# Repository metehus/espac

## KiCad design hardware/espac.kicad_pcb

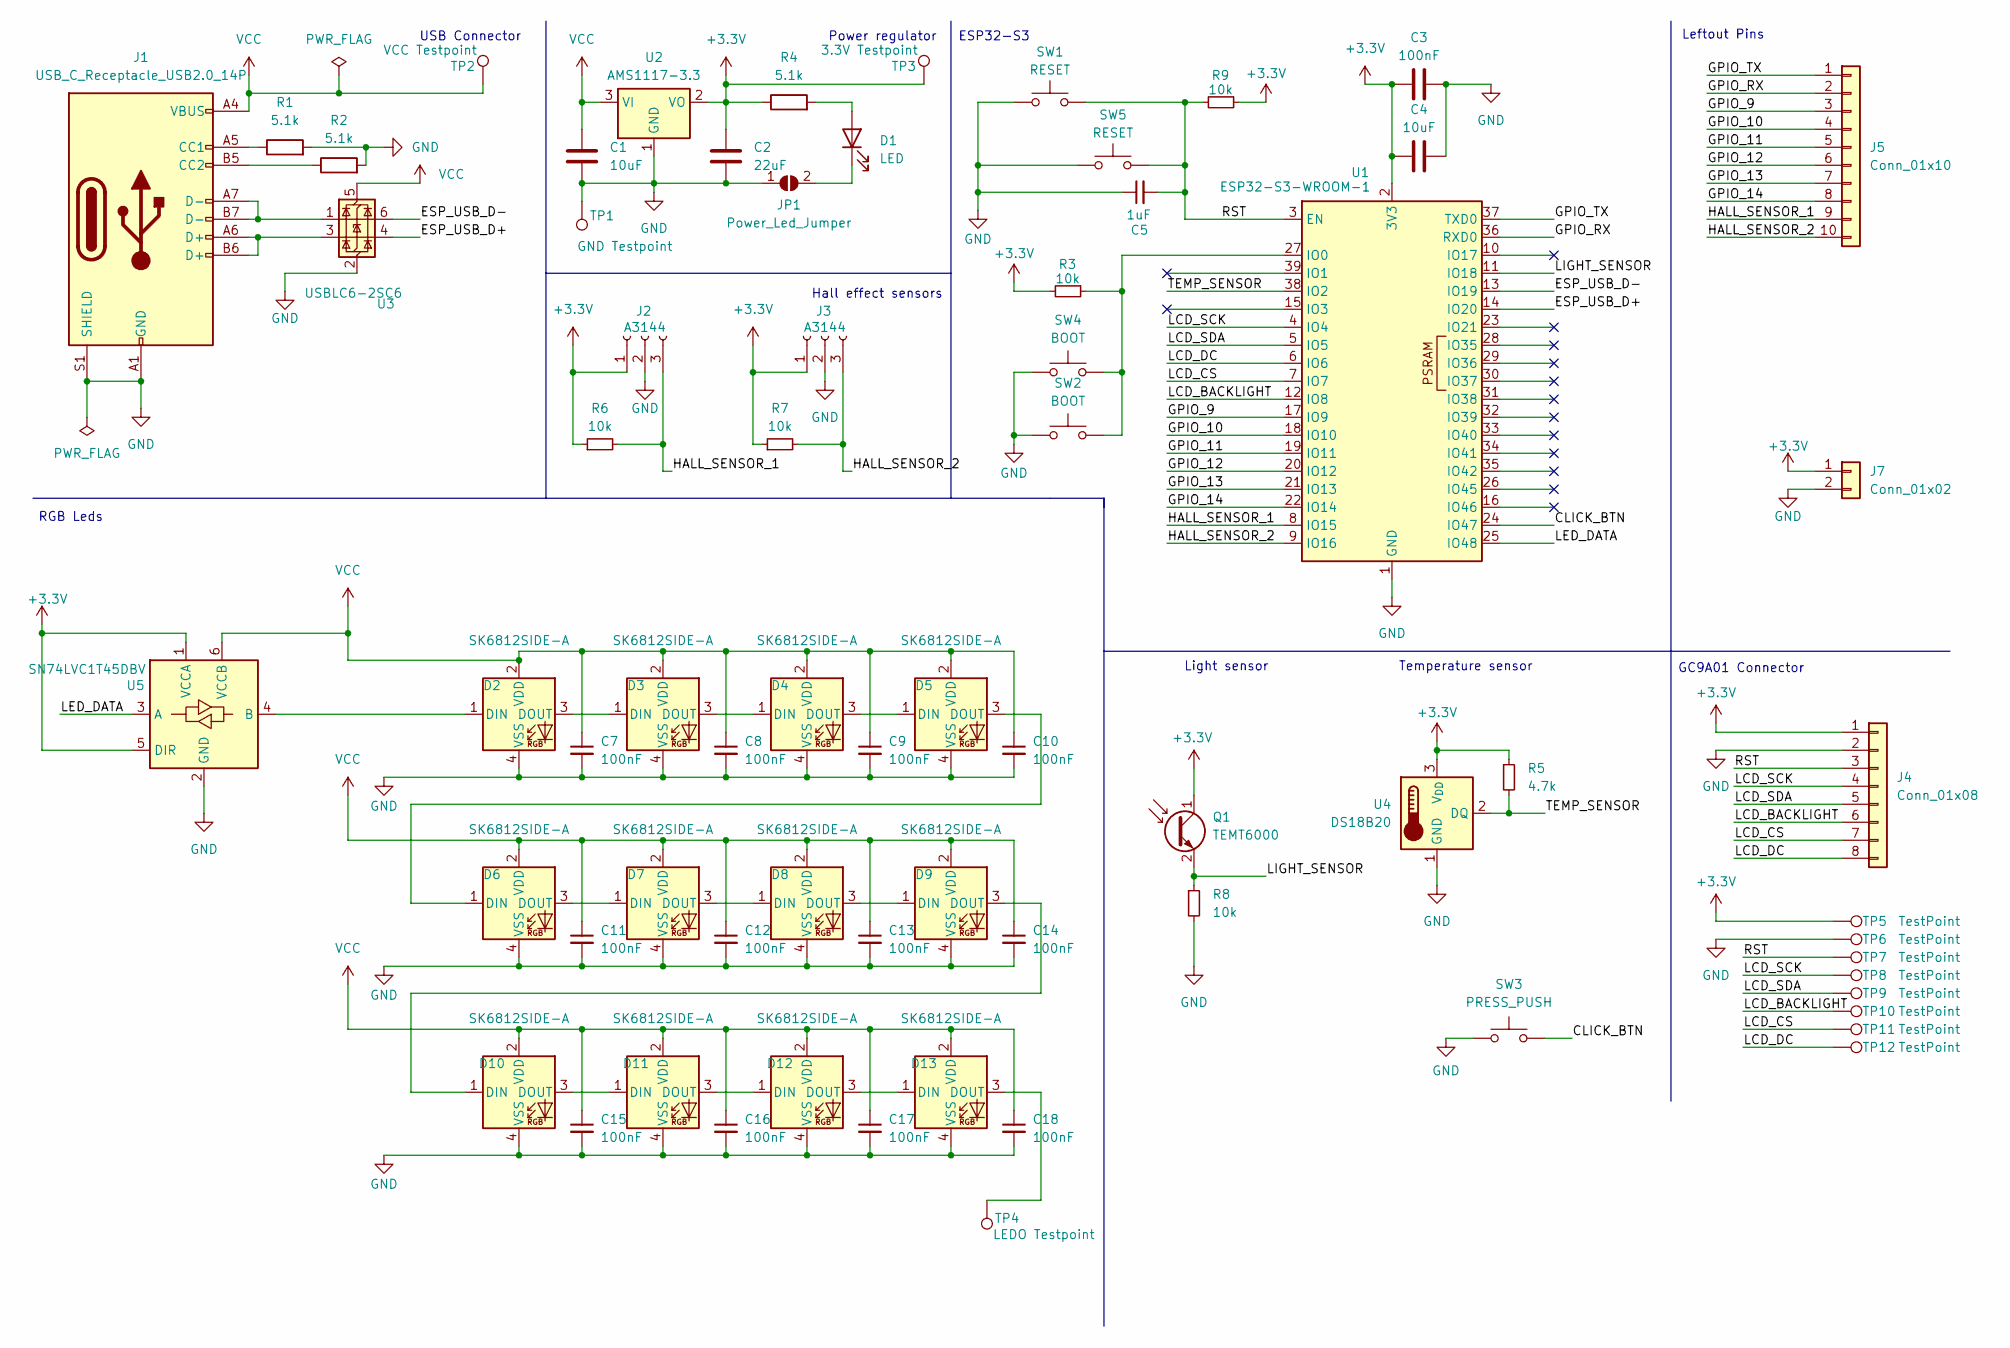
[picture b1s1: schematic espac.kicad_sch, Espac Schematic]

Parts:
C1, C4: 10uF; C_0805_2012Metric_Pad1.18x1.45mm_HandSolder
C2: 22uF; C_0805_2012Metric_Pad1.18x1.45mm_HandSolder
C3, C7, C8, C9, C10, C11, C12, C13, C14, C15, C16, C17, C18: 100nF; C_0805_2012Metric_Pad1.18x1.45mm_HandSolder
C5: 1uF; C_0805_2012Metric_Pad1.18x1.45mm_HandSolder
D1: LED; LED_0603_1608Metric_Pad1.05x0.95mm_HandSolder
D2, D3, D4, D5, D6, D7, D8, D9, D10, D11, D12, D13: SK6812SIDE-A; SK6812-SIDE-A
J1: USB_C_Receptacle_USB2.0_14P; USB_C_Receptacle_G-Switch_GT-USB-7010ASV
J2, J3: A3144; JST_GH_SM03B-GHS-TB_1x03-1MP_P1.25mm_Horizontal
J4: Conn_01x08; TE_0-1734839-8_1x08-1MP_P0.5mm_Horizontal
J5: Conn_01x10; PinSocket_1x10_P2.54mm_Vertical
J7: Conn_01x02; PinHeader_1x02_P2.54mm_Vertical
JP1: Power_Led_Jumper; SolderJumper-2_P1.3mm_Open_RoundedPad1.0x1.5mm
Q1: TEMT6000
R1, R2, R4: 5.1k; R_0603_1608Metric
R3, R6, R7, R8, R9: 10k; R_0603_1608Metric
R5: 4.7k; R_0603_1608Metric
SW1: RESET; SMD_SIDED_TACT_SWITCH
SW2: BOOT; SMD_SIDED_TACT_SWITCH
SW3: PRESS_PUSH; SW_PUSH_6mm_H4.3mm
SW4: BOOT; SMD_TACT_SWITCH
SW5: RESET; SMD_TACT_SWITCH
TP1: GND Testpoint; TestPoint_Pad_D1.5mm
TP2: VCC Testpoint; TestPoint_Pad_D1.5mm
TP3: 3.3V Testpoint; TestPoint_Pad_D1.5mm
TP4: LEDO Testpoint; TestPoint_Pad_D1.5mm
TP5, TP6, TP7, TP8, TP9, TP10, TP11, TP12: TestPoint; TestPoint_Pad_D1.5mm
U1: ESP32-S3-WROOM-1
U2: AMS1117-3.3; SOT-223-3_TabPin2
U3: USBLC6-2SC6; SOT-23-6
U4: DS18B20; TO-92_Inline
U5: SN74LVC1T45DBV; SOT-23-6_Handsoldering

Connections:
+3.3V: C2.1, C3.1, C4.1, J2.1, J3.1, J4.1, J7.1, Q1.1 (C), R3.2, R4.1, R5.1, R6.1, R7.1, R9.1, TP3.1, TP5.1, U1.2 (3V3), U2.2 (VO), U4.3 (V_{DD}), U5.1 (VCCA), U5.5 (DIR)
/CLICK_BTN: SW3.2, U1.24 (IO47)
/ESP_USB_D+: U1.14 (IO20), U3.4 (I/O2)
/ESP_USB_D-: U1.13 (IO19), U3.6 (I/O1)
/GPIO_9: J5.3, U1.17 (IO9)
/GPIO_10: J5.4, U1.18 (IO10)
/GPIO_11: J5.5, U1.19 (IO11)
/GPIO_12: J5.6, U1.20 (IO12)
/GPIO_13: J5.7, U1.21 (IO13)
/GPIO_14: J5.8, U1.22 (IO14)
/GPIO_RX: J5.2, U1.36 (RXD0)
/GPIO_TX: J5.1, U1.37 (TXD0)
/HALL_SENSOR_1: J2.3, J5.9, R6.2, U1.8 (IO15)
/HALL_SENSOR_2: J3.3, J5.10, R7.2, U1.9 (IO16)
/LCD_BACKLIGHT: J4.6, TP10.1, U1.12 (IO8)
/LCD_CS: J4.7, TP11.1, U1.7 (IO7)
/LCD_DC: J4.8, TP12.1, U1.6 (IO6)
/LCD_SCK: J4.4, TP8.1, U1.4 (IO4)
/LCD_SDA: J4.5, TP9.1, U1.5 (IO5)
/LED_DATA: U1.25 (IO48), U5.3 (A)
/LIGHT_SENSOR: Q1.2 (E), R8.1, U1.11 (IO18)
/RST: C5.2, J4.3, R9.2, SW1.2, SW5.1, TP7.1, U1.3 (EN)
/TEMP_SENSOR: R5.2, U1.38 (IO2), U4.2 (DQ)
GND: C1.2, C2.2, C3.2, C4.2, C5.1, C7.2, C8.2, C9.2, C10.2, C11.2, C12.2, C13.2, C14.2, C15.2, C16.2, C17.2, C18.2, D2.4 (VSS), D3.4 (VSS), D4.4 (VSS), D5.4 (VSS), D6.4 (VSS), D7.4 (VSS), D8.4 (VSS), D9.4 (VSS), D10.4 (VSS), D11.4 (VSS), D12.4 (VSS), D13.4 (VSS), J1.A1 (GND), J1.A12 (GND), J1.B1 (GND), J1.B12 (GND), J1.S1 (SHIELD), J2.2, J3.2, J4.2, J7.2, JP1.1 (A), R1.2, R2.2, R8.2, SW1.1, SW2.1, SW3.1, SW4.2, SW5.2, TP1.1, TP6.1, U1.1 (GND), U1.40 (GND), U1.41 (GND), U2.1 (GND), U3.2 (GND), U4.1 (GND), U5.2 (GND)
unnamed: D1.2 (A), R4.2
unnamed: D1.1 (K), JP1.2 (B)
unnamed: D2.1 (DIN), U5.4 (B)
unnamed: D2.3 (DOUT), D3.1 (DIN)
unnamed: D3.3 (DOUT), D4.1 (DIN)
unnamed: D4.3 (DOUT), D5.1 (DIN)
unnamed: D5.3 (DOUT), D6.1 (DIN)
unnamed: D6.3 (DOUT), D7.1 (DIN)
unnamed: D7.3 (DOUT), D8.1 (DIN)
unnamed: D8.3 (DOUT), D9.1 (DIN)
unnamed: D9.3 (DOUT), D10.1 (DIN)
unnamed: D10.3 (DOUT), D11.1 (DIN)
unnamed: D11.3 (DOUT), D12.1 (DIN)
unnamed: D12.3 (DOUT), D13.1 (DIN)
unnamed: D13.3 (DOUT), TP4.1
unnamed: J1.A5 (CC1), R1.1
unnamed: J1.B5 (CC2), R2.1
unnamed: J1.A6 (D+), J1.B6 (D+), U3.3 (I/O2)
unnamed: J1.A7 (D-), J1.B7 (D-), U3.1 (I/O1)
unnamed: R3.1, SW2.2, SW4.1, U1.27 (IO0)
VCC: C1.1, C7.1, C8.1, C9.1, C10.1, C11.1, C12.1, C13.1, C14.1, C15.1, C16.1, C17.1, C18.1, D2.2 (VDD), D3.2 (VDD), D4.2 (VDD), D5.2 (VDD), D6.2 (VDD), D7.2 (VDD), D8.2 (VDD), D9.2 (VDD), D10.2 (VDD), D11.2 (VDD), D12.2 (VDD), D13.2 (VDD), J1.A4 (VBUS), J1.A9 (VBUS), J1.B4 (VBUS), J1.B9 (VBUS), TP2.1, U2.3 (VI), U3.5 (VBUS), U5.6 (VCCB)

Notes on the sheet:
GC9A01 Connector
ESP32-S3
Temperature sensor
USB Connector
Leftout Pins
Hall effect sensors
RGB Leds
Light sensor
Power regulator

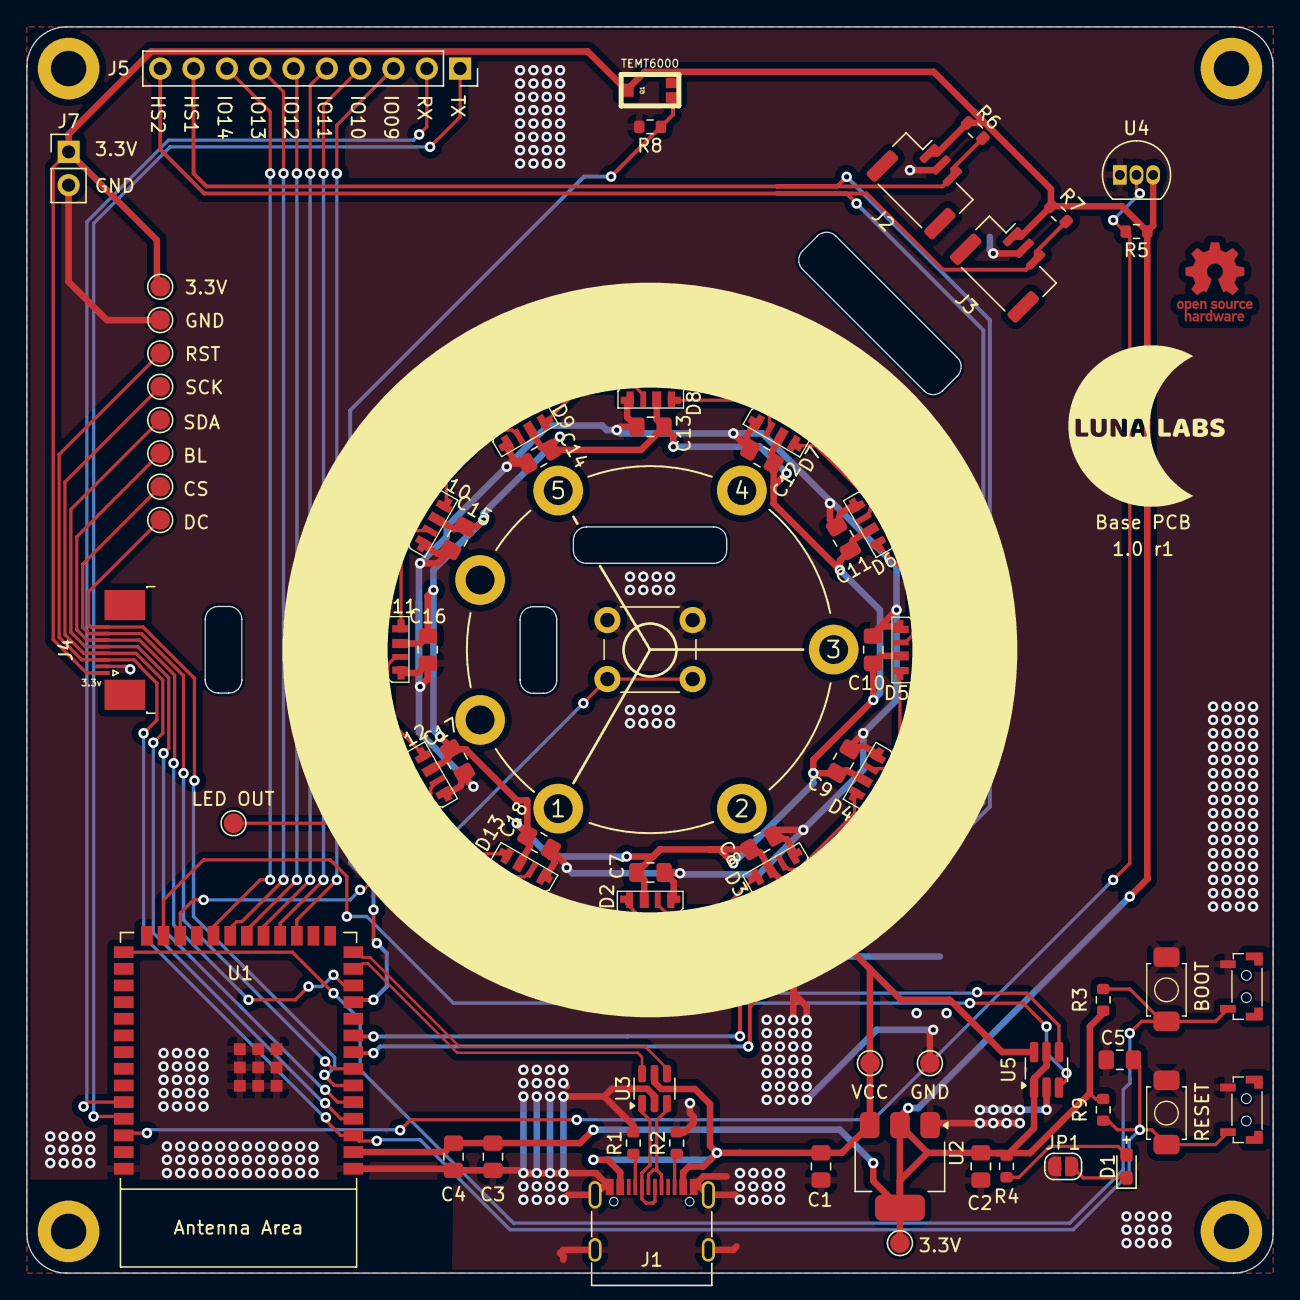
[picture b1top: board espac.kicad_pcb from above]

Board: 2 copper layers, 95.0 x 95.0 mm, 74 parts (0 on the bottom side), 45 nets.

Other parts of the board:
1, 2, 3, 4, 5: (no value)

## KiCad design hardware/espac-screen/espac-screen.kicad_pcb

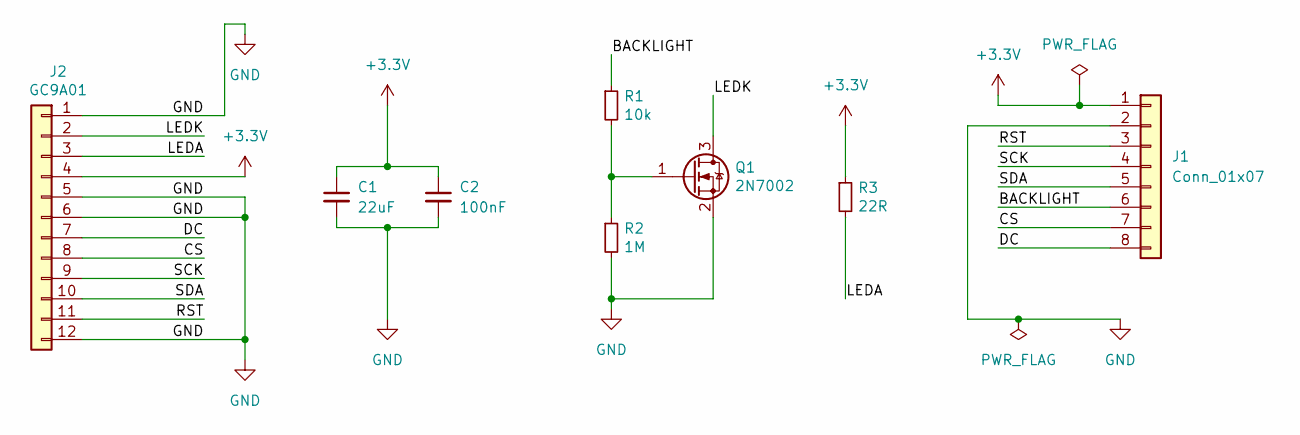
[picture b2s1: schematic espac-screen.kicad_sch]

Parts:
C1: 22uF; C_0805_2012Metric
C2: 100nF; C_0805_2012Metric
J1: Conn_01x07; TE_0-1734839-8_1x08-1MP_P0.5mm_Horizontal
J2: GC9A01; GC9A01Round1.28; Digikey N/A
Q1: 2N7002; SOT-23; Digikey 2N7002H6327XTSA2CT-ND
R1: 10k; R_0603_1608Metric; Digikey RMCF0603JT10K0CT-ND
R2: 1M; R_0603_1608Metric; Digikey RMCF0603JT1M00CT-ND
R3: 22R; R_0603_1608Metric; Digikey RMCF0603JT22R0CT-ND

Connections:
+3.3V: C1.1, C2.1, J1.1, J2.4, R3.1
/BACKLIGHT: J1.6, R1.1
/CS: J1.7, J2.8
/DC: J1.8, J2.7
/LEDA: J2.3, R3.2
/LEDK: J2.2, Q1.3 (D)
/RST: J1.3, J2.11
/SCK: J1.4, J2.9
/SDA: J1.5, J2.10
GND: C1.2, C2.2, J1.2, J2.1, J2.5, J2.6, J2.12, Q1.2 (S), R2.2
unnamed: Q1.1 (G), R1.2, R2.1

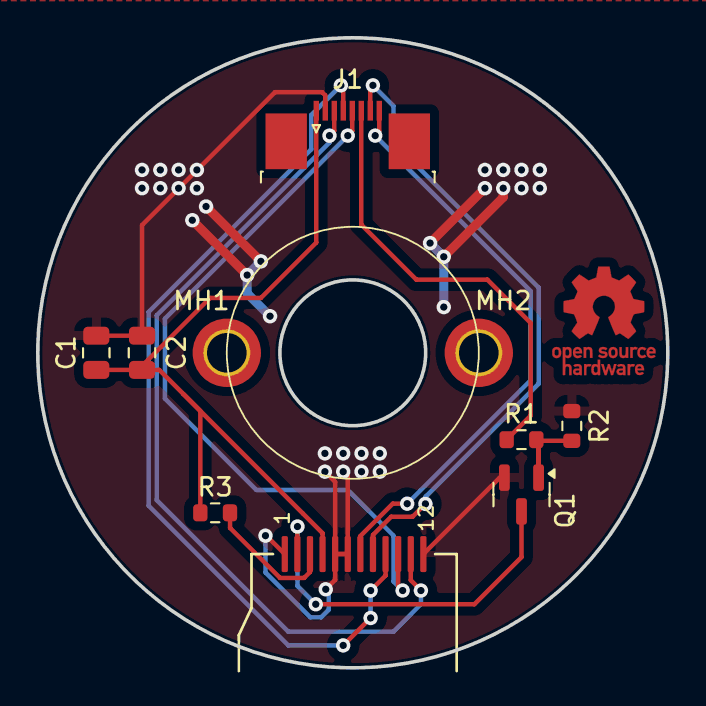
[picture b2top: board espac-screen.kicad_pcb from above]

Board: 2 copper layers, 35.0 x 35.0 mm, 10 parts (0 on the bottom side), 11 nets.

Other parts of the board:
MH1, MH2: MH M2; MountingHole_2.2mm_M2_DIN965_Pad_TopBottom

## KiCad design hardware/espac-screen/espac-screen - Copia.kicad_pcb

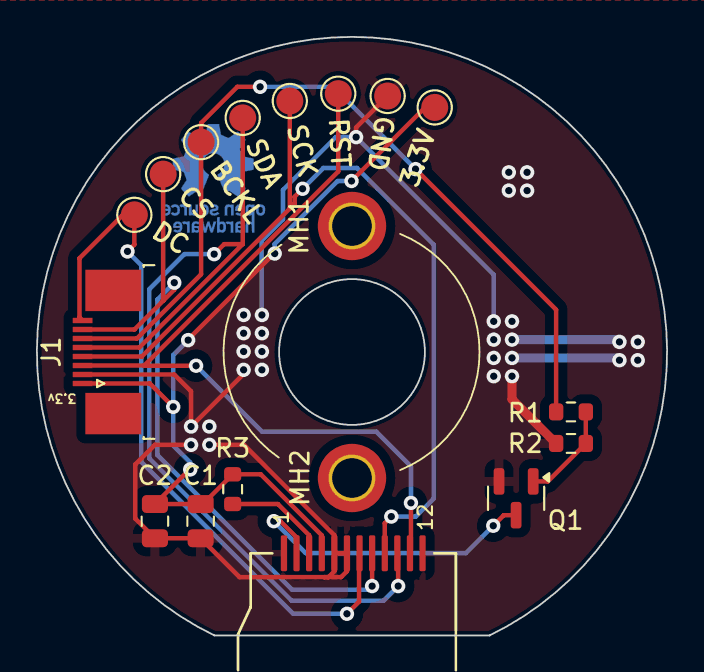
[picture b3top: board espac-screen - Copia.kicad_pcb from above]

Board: 2 copper layers, 35.0 x 33.3 mm, 18 parts (0 on the bottom side), 11 nets.

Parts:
C1: 22uF; C_0805_2012Metric
C2: 100nF; C_0805_2012Metric
J1: Conn_01x07; TE_0-1734839-8_1x08-1MP_P0.5mm_Horizontal
J2: GC9A01; GC9A01Round1.28
MH1, MH2: MH M2; MountingHole_2.2mm_M2_DIN965_Pad_TopBottom
Q1: 2N7002; SOT-23
R1: 10k; R_0603_1608Metric
R2: 1M; R_0603_1608Metric
R3: 22R; R_0603_1608Metric
TP1, TP2, TP3, TP4, TP5, TP6, TP7, TP8: TestPoint; TestPoint_Pad_D1.5mm

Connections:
+3.3V: C1.1, C2.1, J1.1, J2.4, R3.1, TP1.1
/BACKLIGHT: J1.6, R1.1, TP6.1
/CS: J1.7, J2.8, TP7.1
/DC: J1.8, J2.7, TP8.1
/LEDA: J2.3, R3.2
/LEDK: J2.2, Q1.3 (D)
/RST: J1.3, J2.11, TP3.1
/SCK: J1.4, J2.9, TP4.1
/SDA: J1.5, J2.10, TP5.1
GND: C1.2, C2.2, J1.2, J2.1, J2.5, J2.6, J2.12, Q1.2 (S), R2.2, TP2.1
unnamed: Q1.1 (G), R1.2, R2.1

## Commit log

2024-02-24 chore: lvgl test
2024-02-24 chore: missing files
2024-02-24 chore: update
2024-02-26 feat: schematic files
2024-03-11 chore: pcb stuff
2024-03-20 schematic changes
2024-03-20 pcb changes
2024-03-22 chore: pcb rework
2024-04-04 chore: pcb updates
2024-04-04 3d model
2024-04-21 chore: rust rebirth
2024-04-21 fix git submodule
2024-05-17 pcb updates
2024-10-03 feat: firmware setup
2024-10-26 feat: firmware pages
